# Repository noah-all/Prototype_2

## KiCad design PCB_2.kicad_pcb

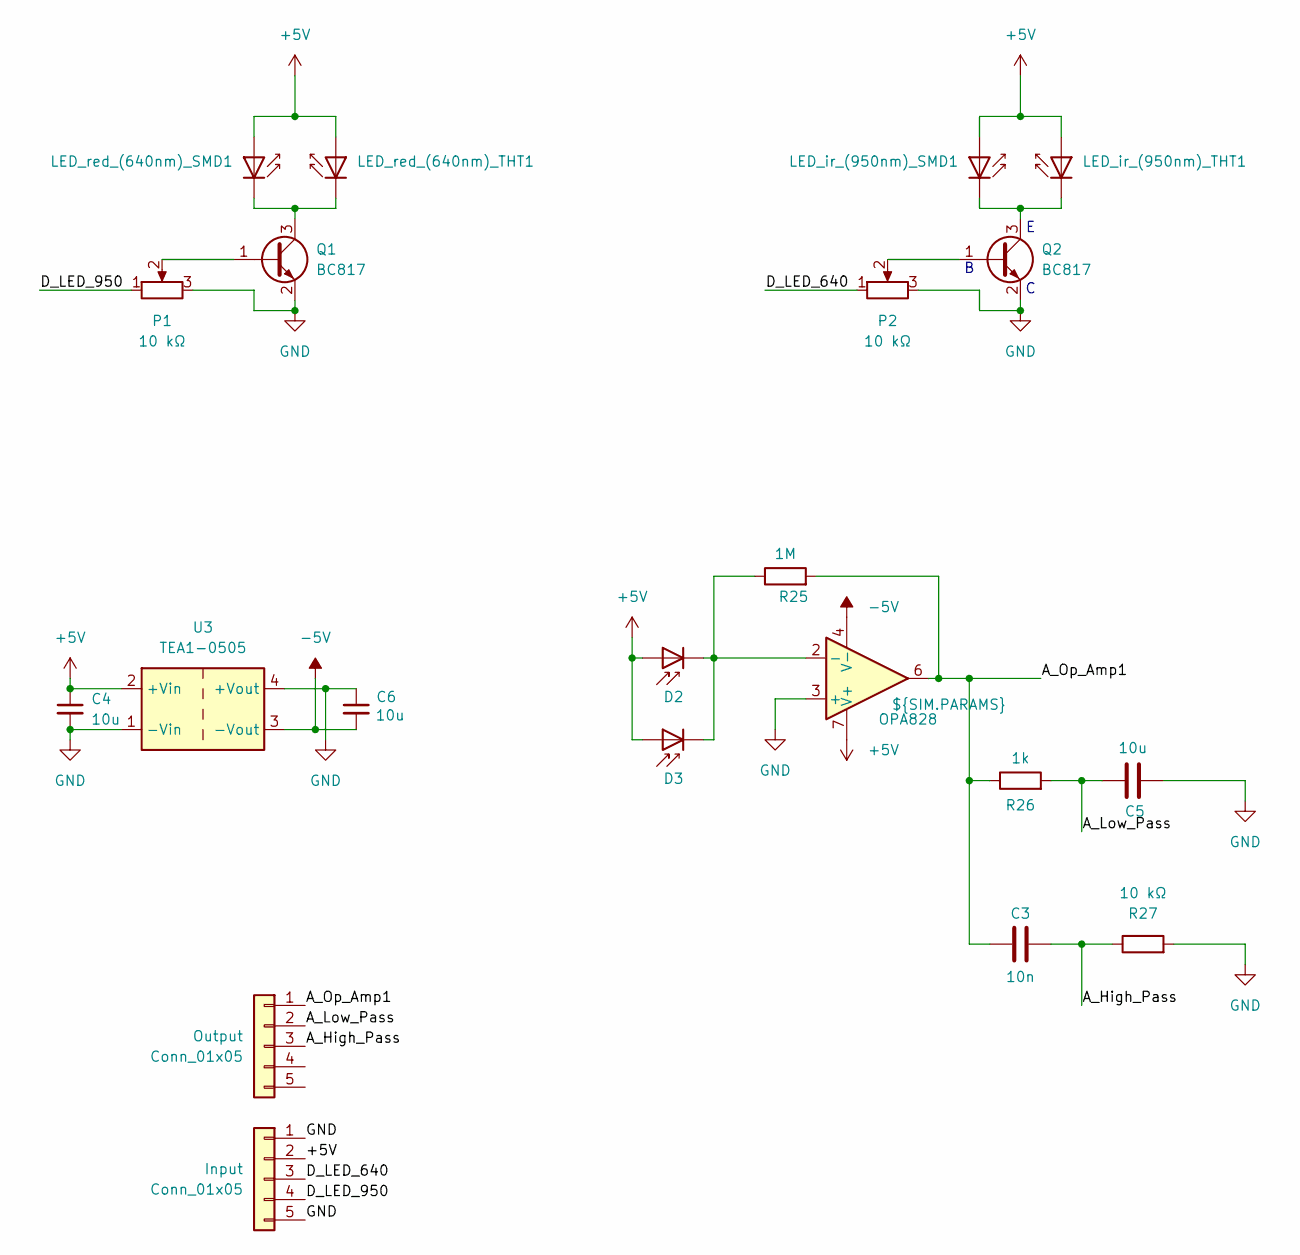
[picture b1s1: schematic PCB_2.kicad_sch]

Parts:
C3: 10n; C_0805_2012Metric
C4, C5, C6: 10u; C_0805_2012Metric
D2: D_Photo; TO-18-2
D3: D_Photo; D_0805_2012Metric_Pad1.15x1.40mm_HandSolder
Input: Conn_01x05; PinHeader_1x05_P2.54mm_Vertical
LED_ir_(950nm)_SMD1: LED_0805_2012Metric
LED_ir_(950nm)_THT1: LED_D5.0mm_IRGrey
LED_red_(640nm)_SMD1: LED_0805_2012Metric
LED_red_(640nm)_THT1: LED_D5.0mm_IRGrey
OPA828: ${SIM.PARAMS}; SOIC-8_3.9x4.9mm_P1.27mm
Output: Conn_01x05; PinHeader_1x05_P2.54mm_Vertical
P1, P2: 10 kΩ; Potentiometer_Bourns_3214W_Vertical
Q1, Q2: BC817; SOT-23
R25: 1M; R_0805_2012Metric
R26: 1k; R_0805_2012Metric
R27: 10 kΩ; C_0805_2012Metric
U3: TEA1-0505; Converter_DCDC_TRACO_TEA1-xxxx_THT

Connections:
+5V: C4.1, D2.2 (A), D3.2 (A), Input.2, LED_ir_(950nm)_SMD1.2 (A), LED_ir_(950nm)_THT1.2 (A), LED_red_(640nm)_SMD1.2 (A), LED_red_(640nm)_THT1.2 (A), OPA828.7 (V+), U3.2 (+Vin)
-5V: C6.2, OPA828.4 (V-), U3.3 (-Vout)
/A_High_Pass: C3.2, Output.3, R27.1
/A_Low_Pass: C5.1, Output.2, R26.2
/A_Op_Amp1: C3.1, OPA828.6, Output.1, R25.2, R26.1
/D_LED_640: Input.3, P2.1
/D_LED_950: Input.4, P1.1
GND: C4.2, C5.2, C6.1, Input.1, Input.5, OPA828.3 (+), P1.3, P2.3, Q1.2 (E), Q2.2 (E), R27.2, U3.1 (-Vin), U3.4 (+Vout)
unnamed: D2.1 (K), D3.1 (K), OPA828.2 (-), R25.1
unnamed: LED_ir_(950nm)_SMD1.1 (K), LED_ir_(950nm)_THT1.1 (K), Q2.3 (C)
unnamed: LED_red_(640nm)_SMD1.1 (K), LED_red_(640nm)_THT1.1 (K), Q1.3 (C)
unnamed: P1.2, Q1.1 (B)
unnamed: P2.2, Q2.1 (B)

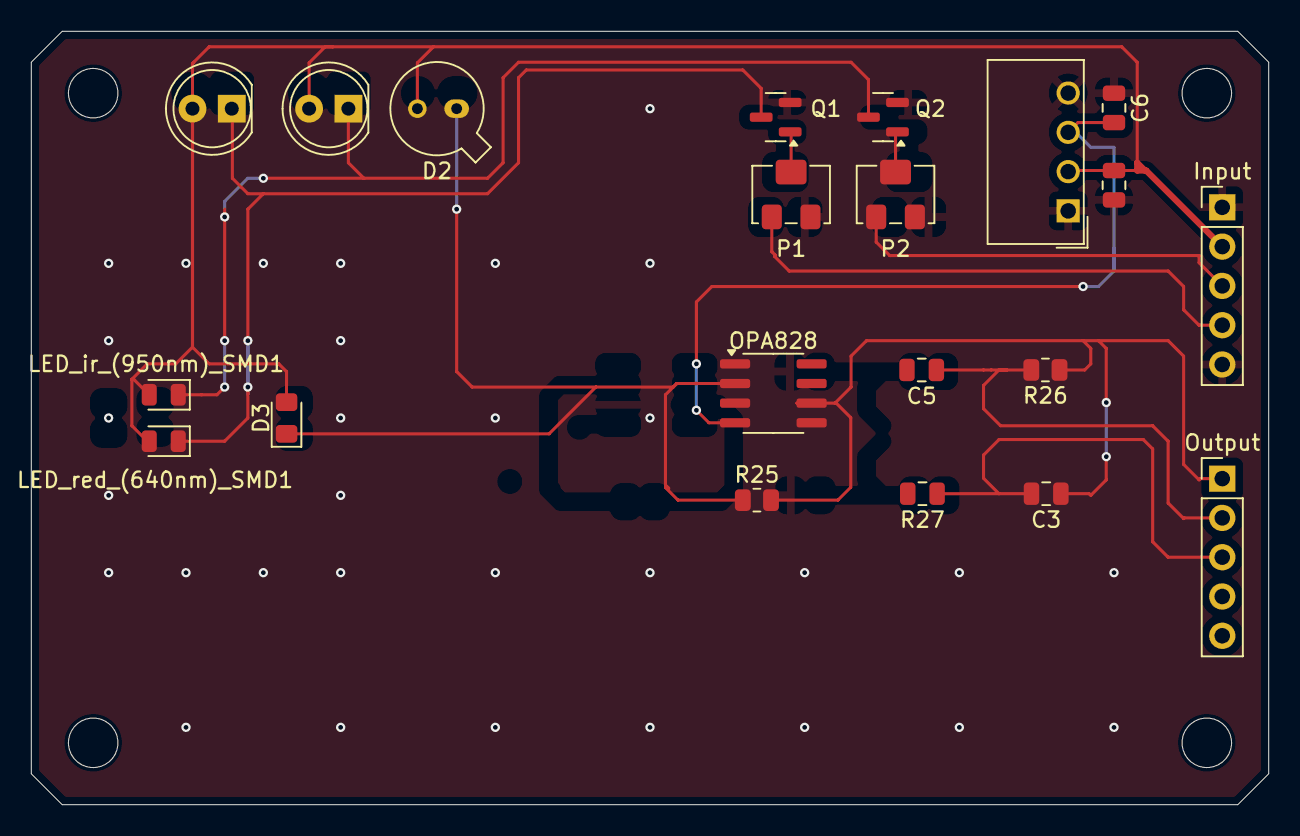
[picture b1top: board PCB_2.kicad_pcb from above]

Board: 2 copper layers, 80.0 x 50.0 mm, 21 parts (0 on the bottom side), 13 nets.

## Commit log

2025-05-02 Updated schematic and layout, cleaned backups
